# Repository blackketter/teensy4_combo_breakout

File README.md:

A combination breakout board with USB-A host and microSD connectors to mate with the [Teensy 4 Header Breakout Board](https://github.com/blackketter/teensy4_header_breakout).  Combines functionality of the [USB Host Breakout](https://github.com/blackketter/teensy4_usb_host_breakout) and the [SD Breakout](https://github.com/blackketter/teensy4_sd_breakout).

It's designed to mount above or below the Teensy 4 and Header Breakout board on a relatively tall header.

Designed in KiCad.

Notes:

- In progress: First cut, seems to work great.
- [OSHPark order](https://oshpark.com/shared_projects/X9b5MPJw)
- Download bom/ibom.html and view it with web browser to see bill of materials and placement information.
- The last pin on the right side provides an optional enable pin for the power management chip on digital pin 27.  For always-on, cut left trace and short right two pads.  
- The last pin on the left side provides SD card detect on digital pin 29.  Needs INPUT_PULLUP.  Cut the jumper to free up pin 29.

Left Side Pinout:

1. 34/SD DAT1
2. 35/SD DAT0
3. GND
4. 36/SD CLK
5. 3.3V
6. 37/SD CMD
7. 38/SD DAT3
8. 39/SD DAT2
9. 29/Card Detect

Right Side Pinout:

1. VUSB
2. USB Host D-
3. USB Host D+
4. GND
5. GND
6. 27/EN

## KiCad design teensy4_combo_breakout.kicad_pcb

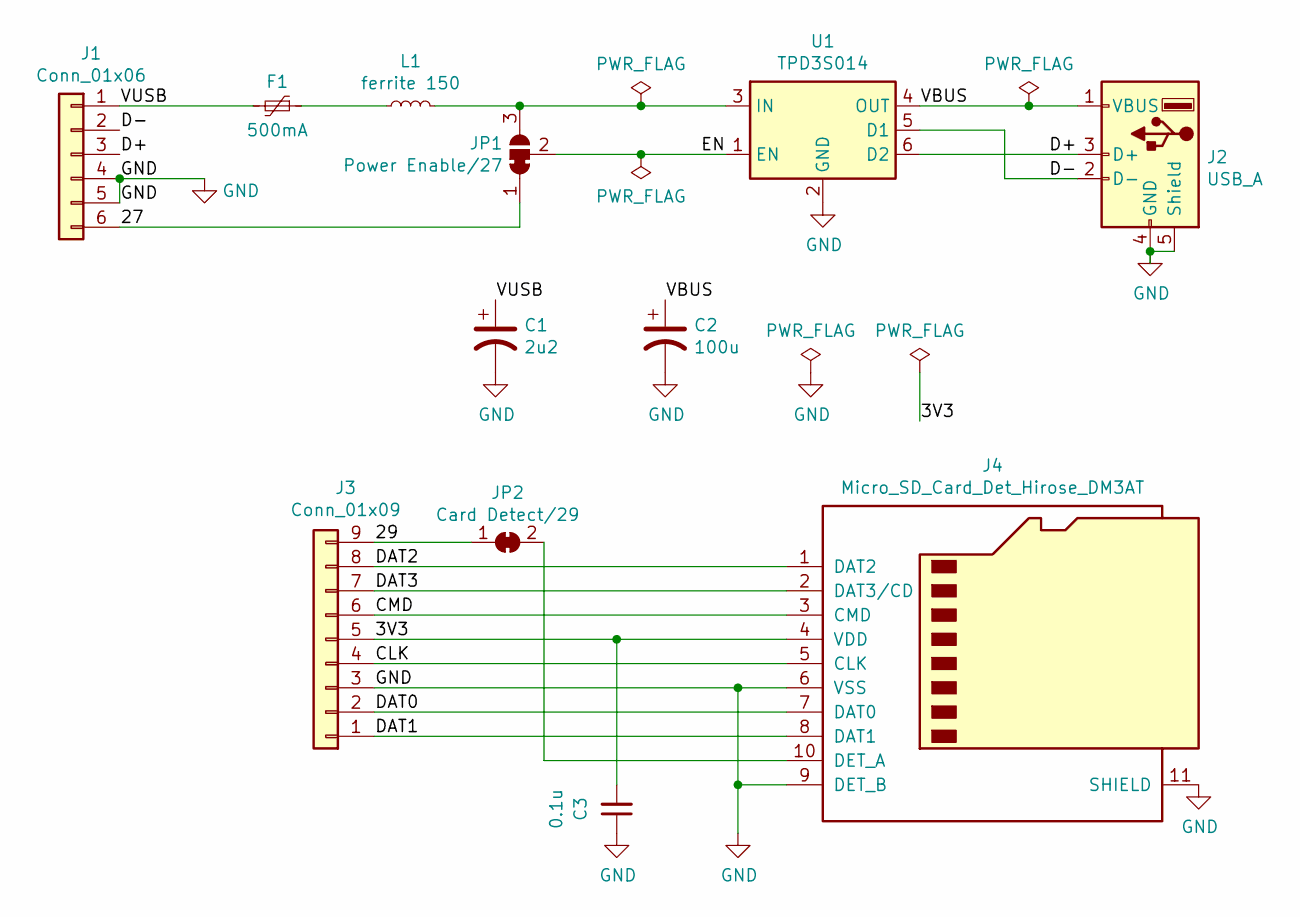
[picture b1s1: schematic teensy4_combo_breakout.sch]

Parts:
C1: 2u2; C_0805_2012Metric_Pad1.15x1.40mm_HandSolder; Digikey 1276-1188-1-ND
C2: 100u; C_1206_3216Metric_Pad1.42x1.75mm_HandSolder; Digikey ‎478-12404-1-ND‎
C3: 0.1u; C_0805_2012Metric_Pad1.15x1.40mm_HandSolder
F1: 500mA; L_0805_2012Metric_Pad1.15x1.40mm_HandSolder; Digikey 507-1813-1-ND
J1: Conn_01x06; PinHeader_1x06_P2.54mm_Vertical
J2: USB_A; USB_A_Receptacle_SMD_Wuerth_629104190121_Narrow; Digikey 732-11179-1-ND
J3: Conn_01x09; PinSocket_1x09_P2.54mm_Vertical
J4: Micro_SD_Card_Det_Hirose_DM3AT; microSD_HC_Hirose_DM3D-SF
JP1: Power Enable/27; SolderJumper-3_P1.3mm_Bridged12_RoundedPad1.0x1.5mm
JP2: Card Detect/29; SolderJumper-2_P1.3mm_Bridged_RoundedPad1.0x1.5mm
L1: ferrite 150; L_0805_2012Metric_Pad1.15x1.40mm_HandSolder; Digikey ‎490-1038-1-ND‎
U1: TPD3S014; SOT-23-6; Digikey 296-38835-1-ND

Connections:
/3V3: C3.2, J3.5, J4.4 (VDD)
/27: J1.6, JP1.1 (A)
/29: J3.9, JP2.1 (A)
/CLK: J3.4, J4.5 (CLK)
/CMD: J3.6, J4.3 (CMD)
/D+: J1.3, J2.3 (D+), U1.6 (D2)
/D-: J1.2, J2.2 (D-), U1.5 (D1)
/DAT0: J3.2, J4.7 (DAT0)
/DAT1: J3.1, J4.8 (DAT1)
/DAT2: J3.8, J4.1 (DAT2)
/DAT3: J3.7, J4.2 (DAT3/CD)
/EN: JP1.2 (C), U1.1 (EN)
/VBUS: C2.1, J2.1 (VBUS), U1.4 (OUT)
/VUSB: C1.1, F1.2, J1.1
GND: C1.2, C2.2, C3.1, J1.4, J1.5, J2.4 (GND), J2.5 (Shield), J3.3, J4.6 (VSS), J4.9 (DET_B), J4.11 (SHIELD), U1.2 (GND)
unnamed: F1.1, L1.1
unnamed: J4.10 (DET_A), JP2.2 (B)
unnamed: JP1.3 (B), L1.2, U1.3 (IN)

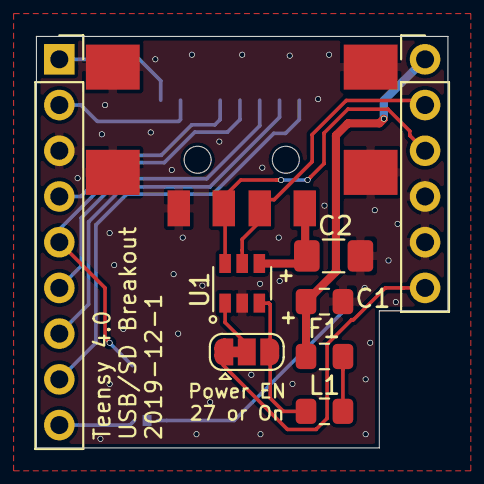
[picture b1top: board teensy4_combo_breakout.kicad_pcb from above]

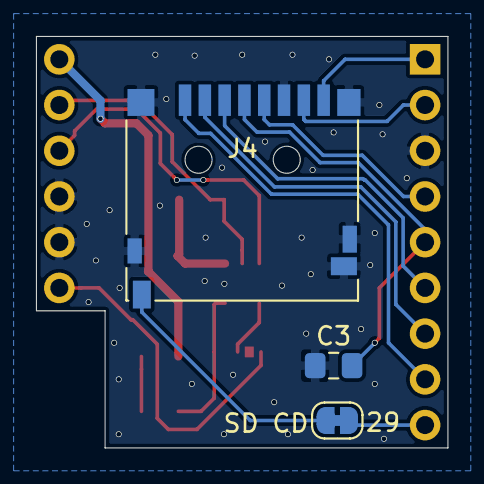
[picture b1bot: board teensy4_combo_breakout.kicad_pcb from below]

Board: 2 copper layers, 22.9 x 22.9 mm, 12 parts (3 on the bottom side), 18 nets.

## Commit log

2019-12-01 First version, ready for fabrication
2019-12-01 Fix board width
2019-12-01 Revert "Fix board width"
    This reverts commit 50ad3588553998c4675441b0cbb2879693a946de.
2019-12-01 Link to OSHPark project
2019-12-04 Reference other breakouts
2020-03-06 Works great
